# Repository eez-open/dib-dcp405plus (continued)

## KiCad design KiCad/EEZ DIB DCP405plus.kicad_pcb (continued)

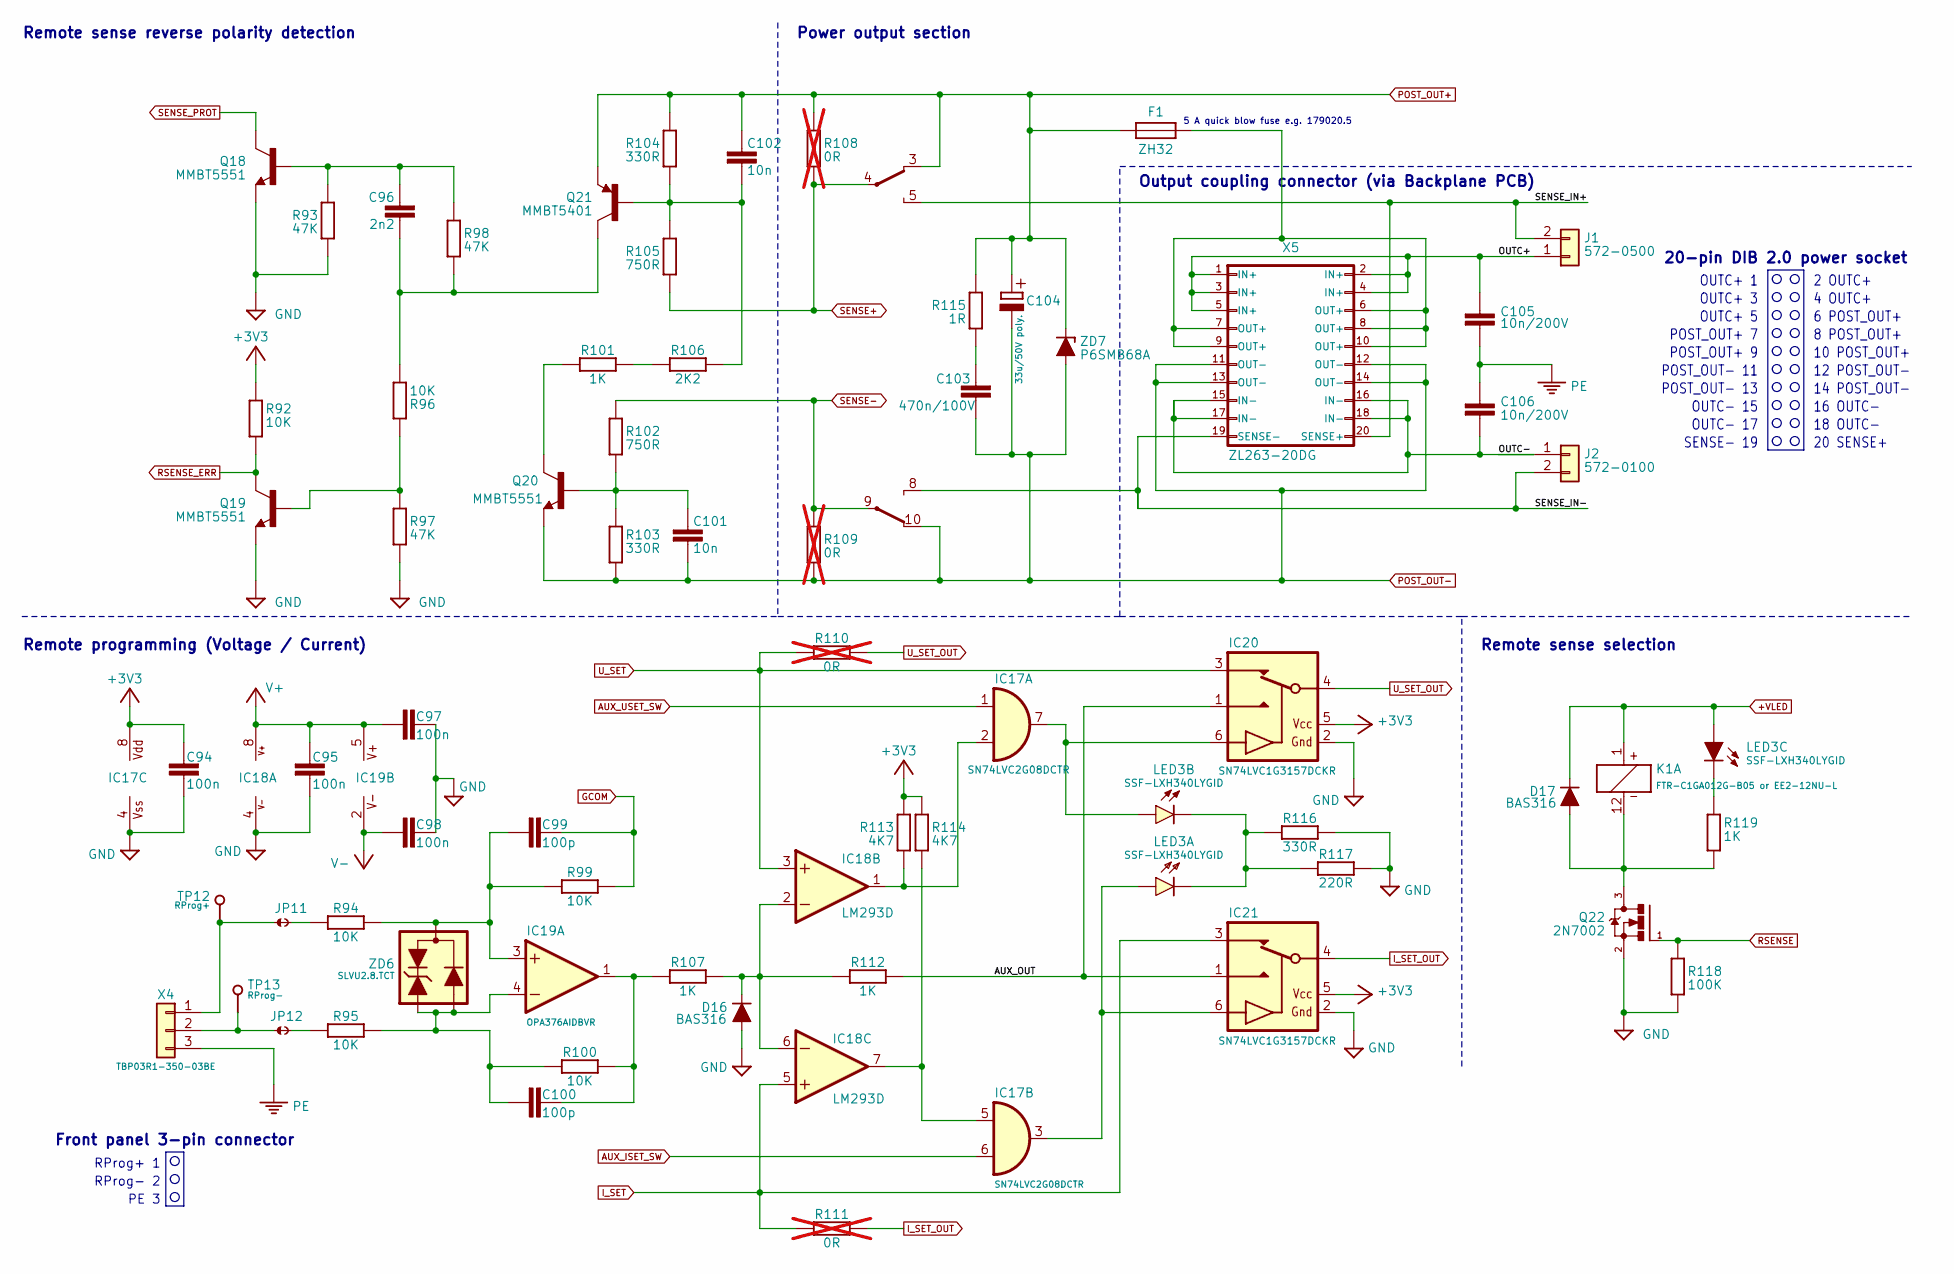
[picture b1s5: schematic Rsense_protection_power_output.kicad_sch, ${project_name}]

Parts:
C94, C95, C97, C98: 100n; C_0603_1608Metric; DigiKey 1276-6717-1-ND
C96: 2n2; C_0805_2012Metric; DigiKey 1276-2478-1-ND
C99, C100: 100p; C_0805_2012Metric; DigiKey 399-15000-1-ND
C101, C102: 10n; C_0805_2012Metric; DigiKey 490-7194-1-ND
C103: 470n/100V; C_0805_2012Metric; DigiKey 587-5014-1-ND
C104: 33u/50V poly.; CAPAE830X1050N; DigiKey 565-HHXD630ARA330MHA0GCT-ND
C105, C106: 10n/200V; C_1206_3216Metric; DigiKey 311-4491-1-ND
D16, D17: BAS316; SOD-323_1P8X1P35_ONS-M; DigiKey 5399-BAS316CT-ND
F1: ZH32; DigiKey 732-11370-ND
IC17: SN74LVC2G08DCTR; DCT8; DigiKey 1727-5987-1-ND
IC18: LM293D; SOIC127P600X173-8N; DigiKey LM293DR2GOSCT-ND
IC19: OPA376AIDBVR; SOT23-5L_STM; DigiKey 296-39130-1-ND
IC20, IC21: SN74LVC1G3157DCKR; SOT65P210X110-6N; DigiKey 296-14909-1-ND
J1: 572-0500; Mouser 164-6221
J2: 572-0100; Mouser 164-6220
JP11, JP12: JP2-NOCUT-0805; JP2 shorted (0603)
K1: FTR-C1GA012G-B05 or EE2-12NU-L; FTR-C1; DigiKey 399-10997-1-ND
LED3: SSF-LXH340LYGID; DigiKey SSF-LXH340LYGID-ND
Q18, Q19, Q20: MMBT5551; SOT23-BEC; DigiKey MMBT5551LT1GOSCT-ND
Q21: MMBT5401; SOT23-BEC; DigiKey MMBT5401-FDICT-ND
Q22: 2N7002; SOT103P240X110-3N; DigiKey T2N7002AKLMCT-ND
R92, R94, R95, R96, R99, R100: 10K; R_0805_2012Metric; DigiKey 311-10.0KCRCT-ND
R93, R97, R98: 47K; R_0805_2012Metric; DigiKey RHM47KKCT-ND
R101, R107, R112, R119: 1K; R_0805_2012Metric; DigiKey 311-1.00KCRCT-ND
R102, R105: 750R; R_0805_2012Metric; DigiKey A126385CT-ND
R103, R104, R116: 330R; R_0805_2012Metric; DigiKey A129743CT-ND
R106: 2K2; R_0805_2012Metric; DigiKey 311-2.20KCRCT-ND
R108, R109, R110, R111: 0R; R_0603_1608Metric; not fitted
R113, R114: 4K7; R_0805_2012Metric; DigiKey 311-4.70KCRCT-ND
R115: 1R; R_0805_2012Metric; DigiKey 13-RC0805FR-131RLCT-ND
R117: 220R; R_0805_2012Metric; DigiKey RMCF0805FT220RCT-ND
R118: 100K; R_0805_2012Metric; DigiKey RMCF0805FT100KCT-ND
TP12, TP13: PCB_TEST_TABSHIELD; Testhole 24_50mils
X4: TBP03R1-350-03BE; DigiKey 2223-TBP03R1-350-03BE-ND
X5: ZL263-20DG; SSW-110-02-T-D-RA; DigiKey PPPC102LJBN-RC
ZD6: SLVU2.8.TCT; SOT23-3; DigiKey SLVU2.8.TCTCT-ND
ZD7: P6SMB68A; DO214AA; DigiKey P6SMB68ABBCT-ND

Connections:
+3V3: C94.2, IC17.8 (VDD), IC20.5 (VDD), IC21.5 (VDD), R92.2, R113.1, R114.1; also elsewhere on the board
+VLED: D17.C, K1.1 (C1), LED3.YA; also elsewhere on the board
/Rsense protection, power output, Rprog/AUX_OUT: IC20.1 (NO), IC21.1 (NO), R112.1
/Rsense protection, power output, Rprog/OUTC+: C105.1, J1.1, X5.1 (IN+), X5.2 (IN+), X5.3 (IN+), X5.4 (IN+), X5.5 (IN+)
/Rsense protection, power output, Rprog/OUTC-: C106.2, J2.1, X5.15 (IN-), X5.16 (IN-), X5.17 (IN-), X5.18 (IN-)
/Rsense protection, power output, Rprog/SENSE_IN+: J1.2, K1.5 (NO), X5.20 (SENSE+)
/Rsense protection, power output, Rprog/SENSE_IN-: J2.2, K1.8 (NO), X5.19 (SENSE-)
AUX_ISET_SW: IC17.6 (I1); also elsewhere on the board
AUX_USET_SW: IC17.1 (I0); also elsewhere on the board
GCOM: C99.1, R99.1; also elsewhere on the board
GND: C94.1, C95.2, C97.2, C98.2, D16.A, IC17.4 (VSS), IC18.4 (V-), IC20.2 (GND), IC21.2 (GND), Q18.E, Q19.E, Q22.2 (S), R93.1, R97.1, R116.1, R117.1, R118.1; also elsewhere on the board
I_SET: IC18.5 (+IN), IC21.3 (NC), R111.2; also elsewhere on the board
I_SET_OUT: IC21.4 (COM), R111.1; also elsewhere on the board
unnamed: C96.1, Q18.B, R93.2, R98.2
unnamed: C96.2, Q21.C, R96.2, R98.1
unnamed: C101.1, Q20.B, R102.1, R103.2
unnamed: C102.2, Q21.B, R104.1, R105.2, R106.2
unnamed: C103.2, R115.2
unnamed: F1.2, X5.6 (OUT+), X5.7 (OUT+), X5.8 (OUT+), X5.9 (OUT+), X5.10 (OUT+)
unnamed: IC17.2 (I1), IC18.1 (OUT), R113.2
unnamed: IC17.7 (O), IC20.6 (CTRL), LED3.GA
unnamed: IC17.5 (I0), IC18.7 (OUT), R114.2
unnamed: IC17.3 (O), IC21.6 (CTRL), LED3.RA
unnamed: D16.C, IC18.2 (-IN), IC18.6 (-IN), R107.1, R112.2
unnamed: C99.2, IC19.3 (+IN), R94.1, R99.2, ZD6.3
unnamed: C100.2, IC19.4 (-IN), R95.1, R100.2, ZD6.1, ZD6.2
unnamed: C100.1, IC19.1 (OUT), R100.1, R107.2
unnamed: JP11.2, R94.2
unnamed: JP12.2, R95.2
unnamed: D17.A, K1.12 (C2), Q22.3 (D), R119.1
unnamed: LED3.GC, LED3.RC, R116.2, R117.2
unnamed: LED3.YC, R119.2
unnamed: Q19.B, R96.1, R97.2
unnamed: Q20.C, R101.1
unnamed: R101.2, R106.1
unnamed: JP11.1, TP12.1 (P$1_1), X4.1
unnamed: JP12.1, TP13.1 (P$1_1), X4.2
PE: C105.2, C106.1, X4.3; also elsewhere on the board
POST_OUT+: C102.1, C104.+, F1.1, K1.3 (NC), Q21.E, R104.2, R108.1, R115.1, ZD7.C; also elsewhere on the board
POST_OUT-: C101.2, C103.1, C104.-, K1.10 (NC), Q20.E, R103.1, R109.2, X5.11 (OUT-), X5.12 (OUT-), X5.13 (OUT-), X5.14 (OUT-), ZD7.A; also elsewhere on the board
RSENSE: Q22.1 (G), R118.2; also elsewhere on the board
RSENSE_ERR: Q19.C, R92.1; also elsewhere on the board
SENSE+: K1.4 (COM), R105.1, R108.2; also elsewhere on the board
SENSE-: K1.9 (COM), R102.2, R109.1; also elsewhere on the board
SENSE_PROT: Q18.C; also elsewhere on the board
U_SET: IC18.3 (+IN), IC20.3 (NC), R110.2; also elsewhere on the board
U_SET_OUT: IC20.4 (COM), R110.1; also elsewhere on the board
V+: C95.1, C97.1, IC18.8 (V+), IC19.5 (V+); also elsewhere on the board
V-: C98.1, IC19.2 (V-); also elsewhere on the board

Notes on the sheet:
8 POST_OUT+
PE 3
16 OUTC-
POST_OUT- 11
12 POST_OUT-
Remote sense reverse polarity detection
POST_OUT+ 9
OUTC- 17
Output coupling connector (via Backplane PCB)
POST_OUT- 13
Remote programming (Voltage / Current)
10 POST_OUT+
4 OUTC+
6 POST_OUT+
2 OUTC+
OUTC+ 5
14 POST_OUT-
18 OUTC-
POST_OUT+ 7
OUTC+ 1
RProg+ 1
20 SENSE+
Front panel 3-pin connector
OUTC+ 3
5 A quick blow fuse e.g. 179020.5
RProg- 2
Power output section
Remote sense selection
SENSE- 19
OUTC- 15
20-pin DIB 2.0 power socket

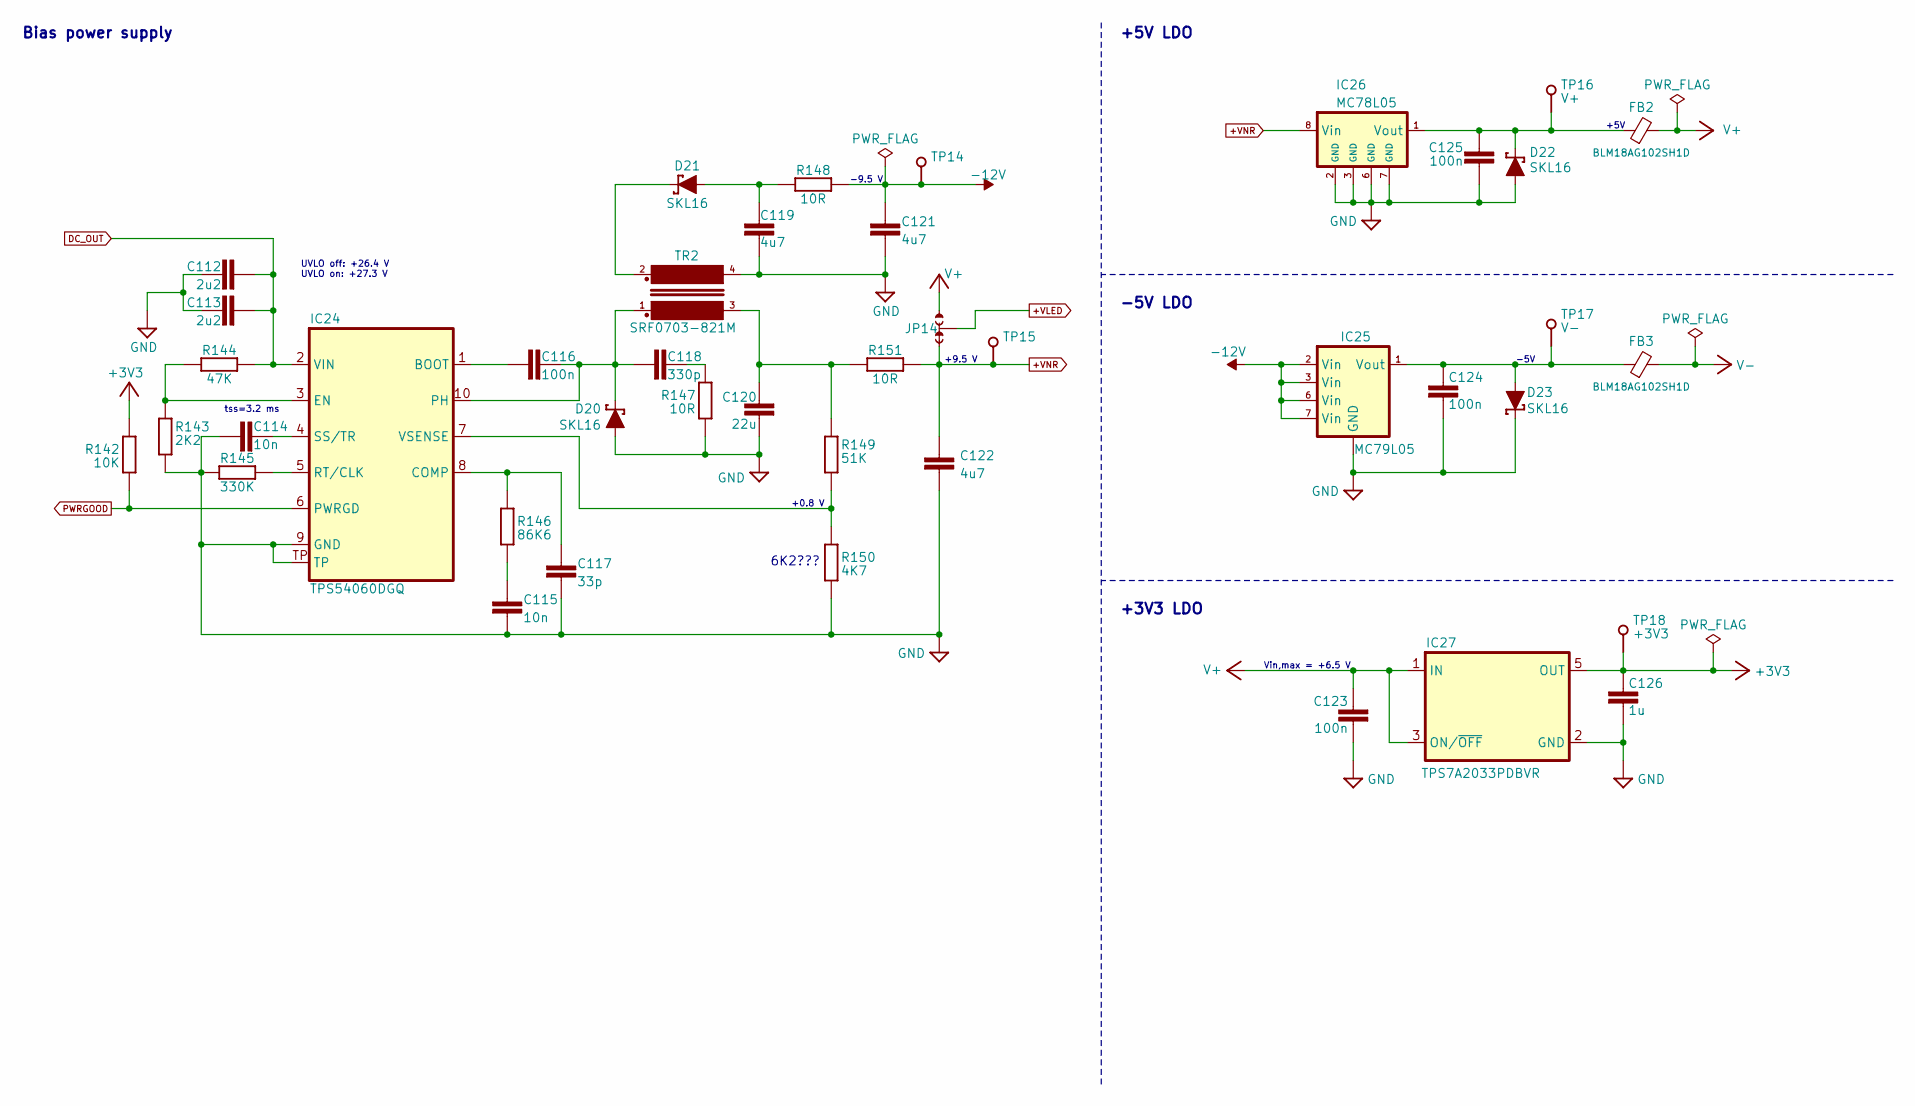
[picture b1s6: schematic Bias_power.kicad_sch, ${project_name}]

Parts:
C112, C113: 2u2; C_1206_3216Metric; DigiKey 1276-3138-1-ND
C114, C115: 10n; C_0805_2012Metric; DigiKey 490-7194-1-ND
C116, C123, C124, C125: 100n; C_0603_1608Metric; DigiKey 1276-6717-1-ND
C117: 33p; C_0805_2012Metric; DigiKey 399-C0805C330J5GACTUCT-ND
C118: 330p; C_0805_2012Metric; DigiKey 311-1117-1-ND
C119, C121, C122: 4u7; C_0805_2012Metric; DigiKey 1276-2415-1-ND
C120: 22u; C_1210_3225Metric; DigiKey 1276-1851-1-ND
C126: 1u; C_0805_2012Metric; DigiKey 1276-2931-1-ND
D20, D21, D22, D23: SKL16; SOD123; DigiKey RB160MM-60CT-ND
FB2, FB3: BLM18AG102SH1D; BEAD0603; DigiKey 490-7809-1-ND
IC24: TPS54060DGQ; SOP50P490X110-11N; DigiKey 296-37148-1-ND
IC25: MC79L05; SOIC127P600X173-8N; DigiKey MC79L05ACDR2GOSCT-ND
IC26: MC78L05; SOIC127P600X173-8N; DigiKey MC78L05ACDR2GOSCT-ND
IC27: TPS7A2033PDBVR; SOT23-5L_STM; DigiKey 296-TPS7A2033PDBVRCT-ND
JP14: JP3 shorted (0603)
R142: 10K; R_0805_2012Metric; DigiKey 311-10.0KCRCT-ND
R143: 2K2; R_0805_2012Metric; DigiKey 311-2.20KCRCT-ND
R144: 47K; R_0805_2012Metric; DigiKey RHM47KKCT-ND
R145: 330K; R_0805_2012Metric; DigiKey A126361CT-ND
R146: 86K6; R_0805_2012Metric; DigiKey 311-86.6KCRCT-ND
R147, R148, R151: 10R; R_0805_2012Metric; DigiKey 311-10.0CRCT-ND
R149: 51K; R_0805_2012Metric; DigiKey 311-51.0KCRCT-ND
R150: 4K7; R_0805_2012Metric; DigiKey 311-4.70KCRCT-ND
TP14, TP15, TP16, TP17, TP18: TEST-PIN_0.9MM; Testhole 24_50mils
TR2: SRF0703-821M; SRF0703; DigiKey SRF0703-821MCT-ND

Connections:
+3V3: C126.2, IC27.5 (OUT), R142.1, TP18.1 (P$1_1); also elsewhere on the board
+VLED: JP14.COM; also elsewhere on the board
+VNR: C122.1, IC26.8 (Vin), JP14.NC, R151.2, TP15.1 (P$1_1); also elsewhere on the board
-12V: C121.1, IC25.2 (Vin), IC25.3 (Vin), IC25.6 (Vin), IC25.7 (Vin), R148.2, TP14.1 (P$1_1); also elsewhere on the board
DC_OUT: C112.1, C113.1, IC24.2 (VIN), R144.2; also elsewhere on the board
GND: C112.2, C113.2, C114.2, C115.1, C117.1, C119.2, C120.2, C121.2, C122.2, C123.1, C124.1, C125.2, C126.1, D20.A, D22.A, D23.C, IC24.9 (GND), IC24.TP, IC25.5 (GND), IC26.2 (GND), IC26.3 (GND), IC26.6 (GND), IC26.7 (GND), IC27.2 (GND), R143.1, R145.1, R147.2, R150.2, TR2.4; also elsewhere on the board
unnamed: C115.2, R146.1
unnamed: C118.2, R147.1
unnamed: C119.1, D21.A, R148.1
unnamed: C120.1, R149.1, R151.1, TR2.3
unnamed: D21.C, TR2.2
unnamed: C116.2, IC24.1 (BOOT)
unnamed: C117.2, IC24.8 (COMP), R146.2
unnamed: IC24.3 (EN), R143.2, R144.1
unnamed: C116.1, C118.1, D20.C, IC24.10 (PH), TR2.1
unnamed: IC24.5 (RT/CLK), R145.2
unnamed: C114.1, IC24.4 (SS/TR)
unnamed: IC24.7 (VSENSE), R149.2, R150.1
unnamed: C124.2, D23.A, FB3.1, IC25.1 (Vout), TP17.1 (P$1_1)
unnamed: C125.1, D22.C, FB2.1, IC26.1 (Vout), TP16.1 (P$1_1)
PWRGOOD: IC24.6 (PWRGD), R142.2; also elsewhere on the board
V+: C123.2, FB2.2, IC27.1 (IN), IC27.3 (ON/~OFF), JP14.NO; also elsewhere on the board
V-: FB3.2; also elsewhere on the board

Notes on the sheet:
+5V
UVLO off: +26.4 V UVLO on: +27.3 V
Vin,max = +6.5 V
+5V LDO
Bias power supply
-5V LDO
+0.8 V
+3V3 LDO
6K2???
-5V
-9.5 V
tss=3.2 ms
+9.5 V

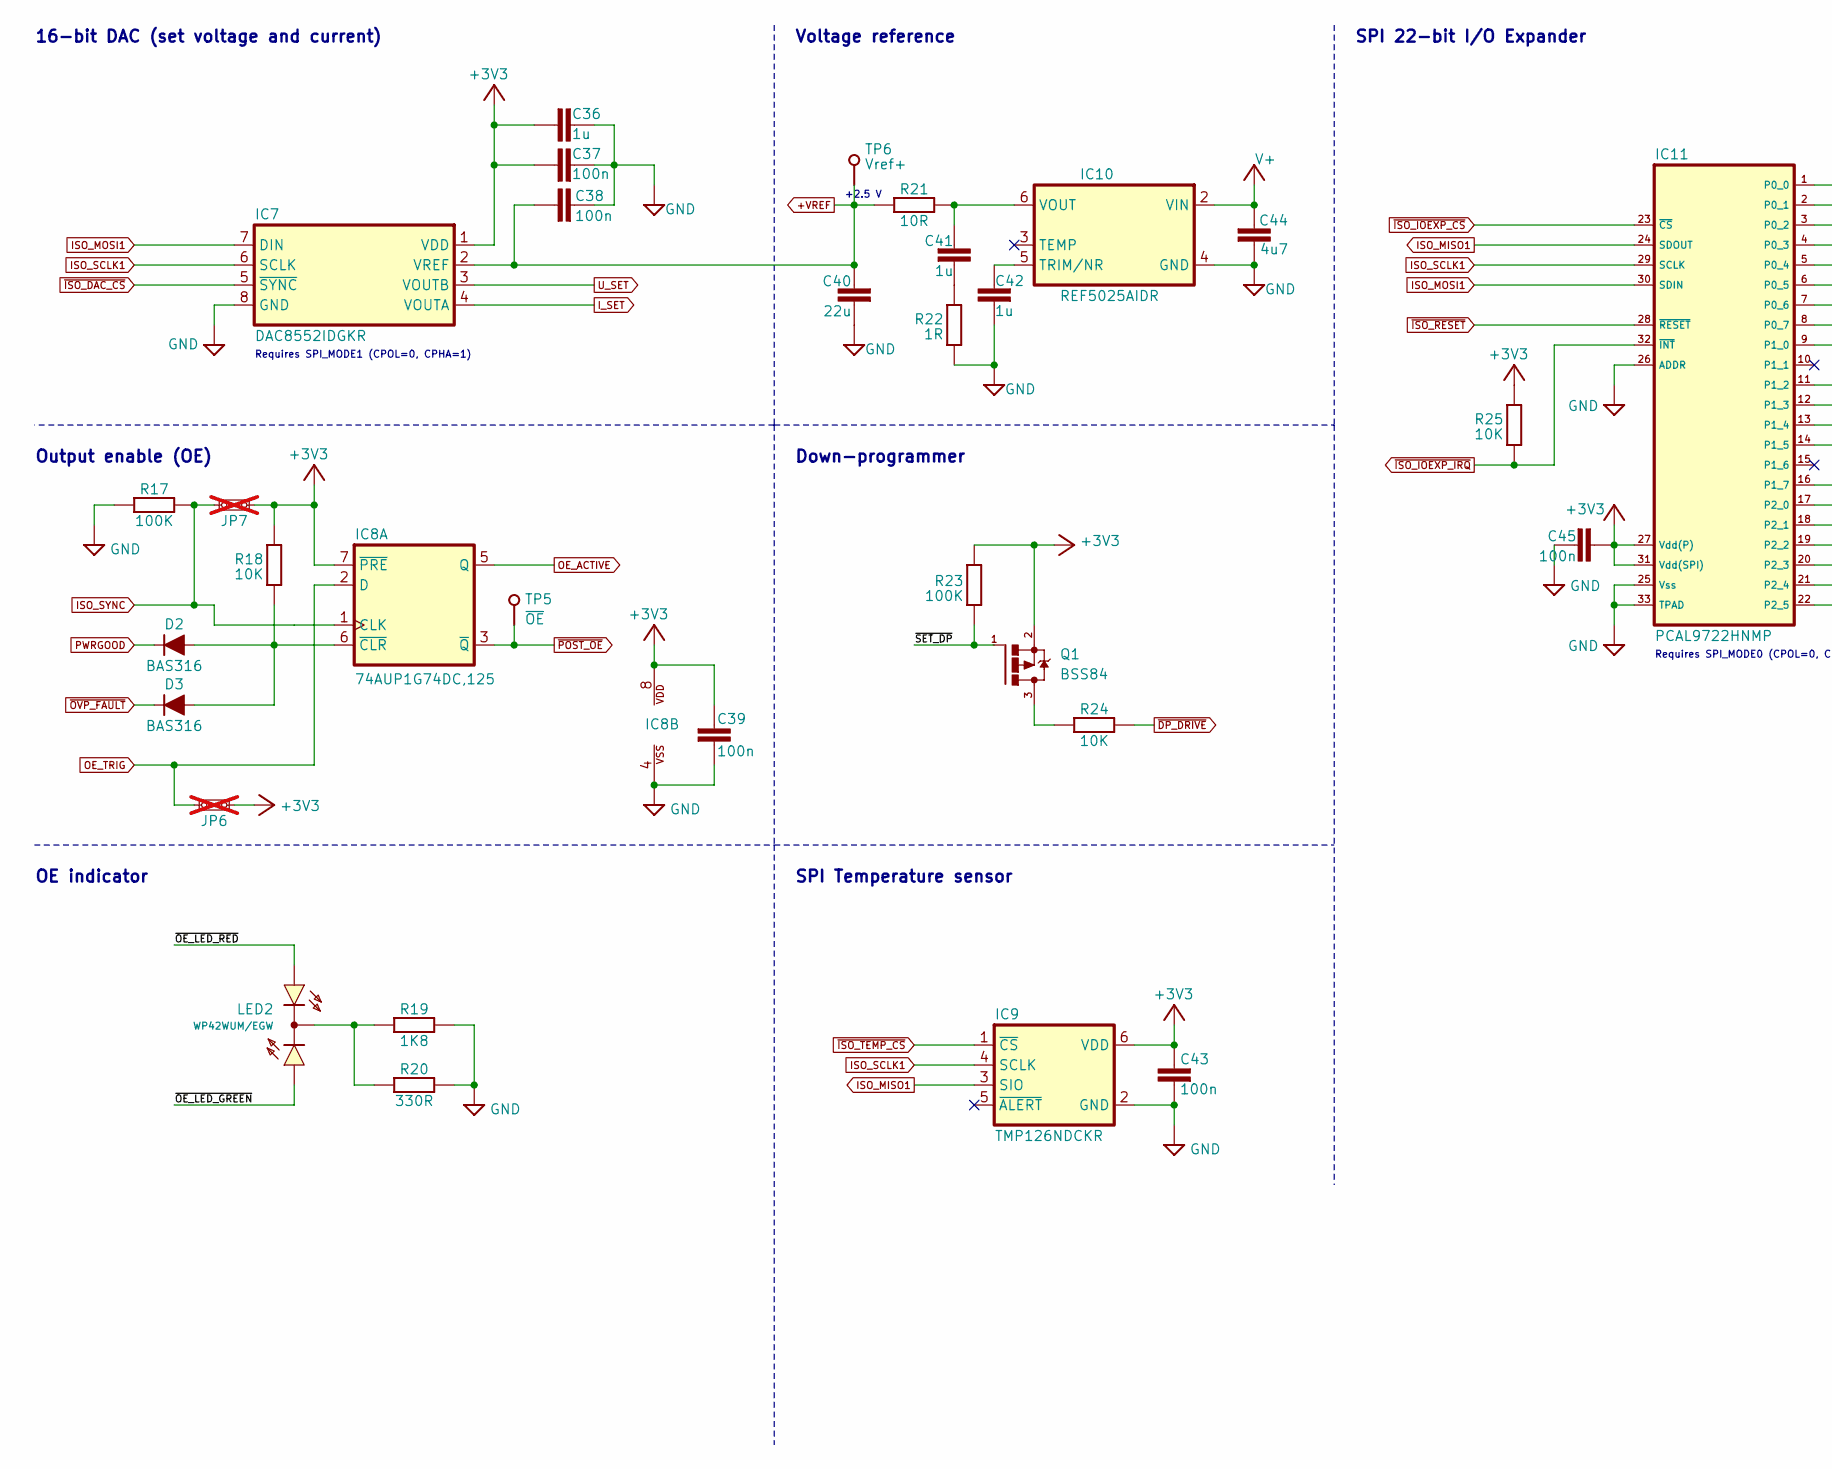
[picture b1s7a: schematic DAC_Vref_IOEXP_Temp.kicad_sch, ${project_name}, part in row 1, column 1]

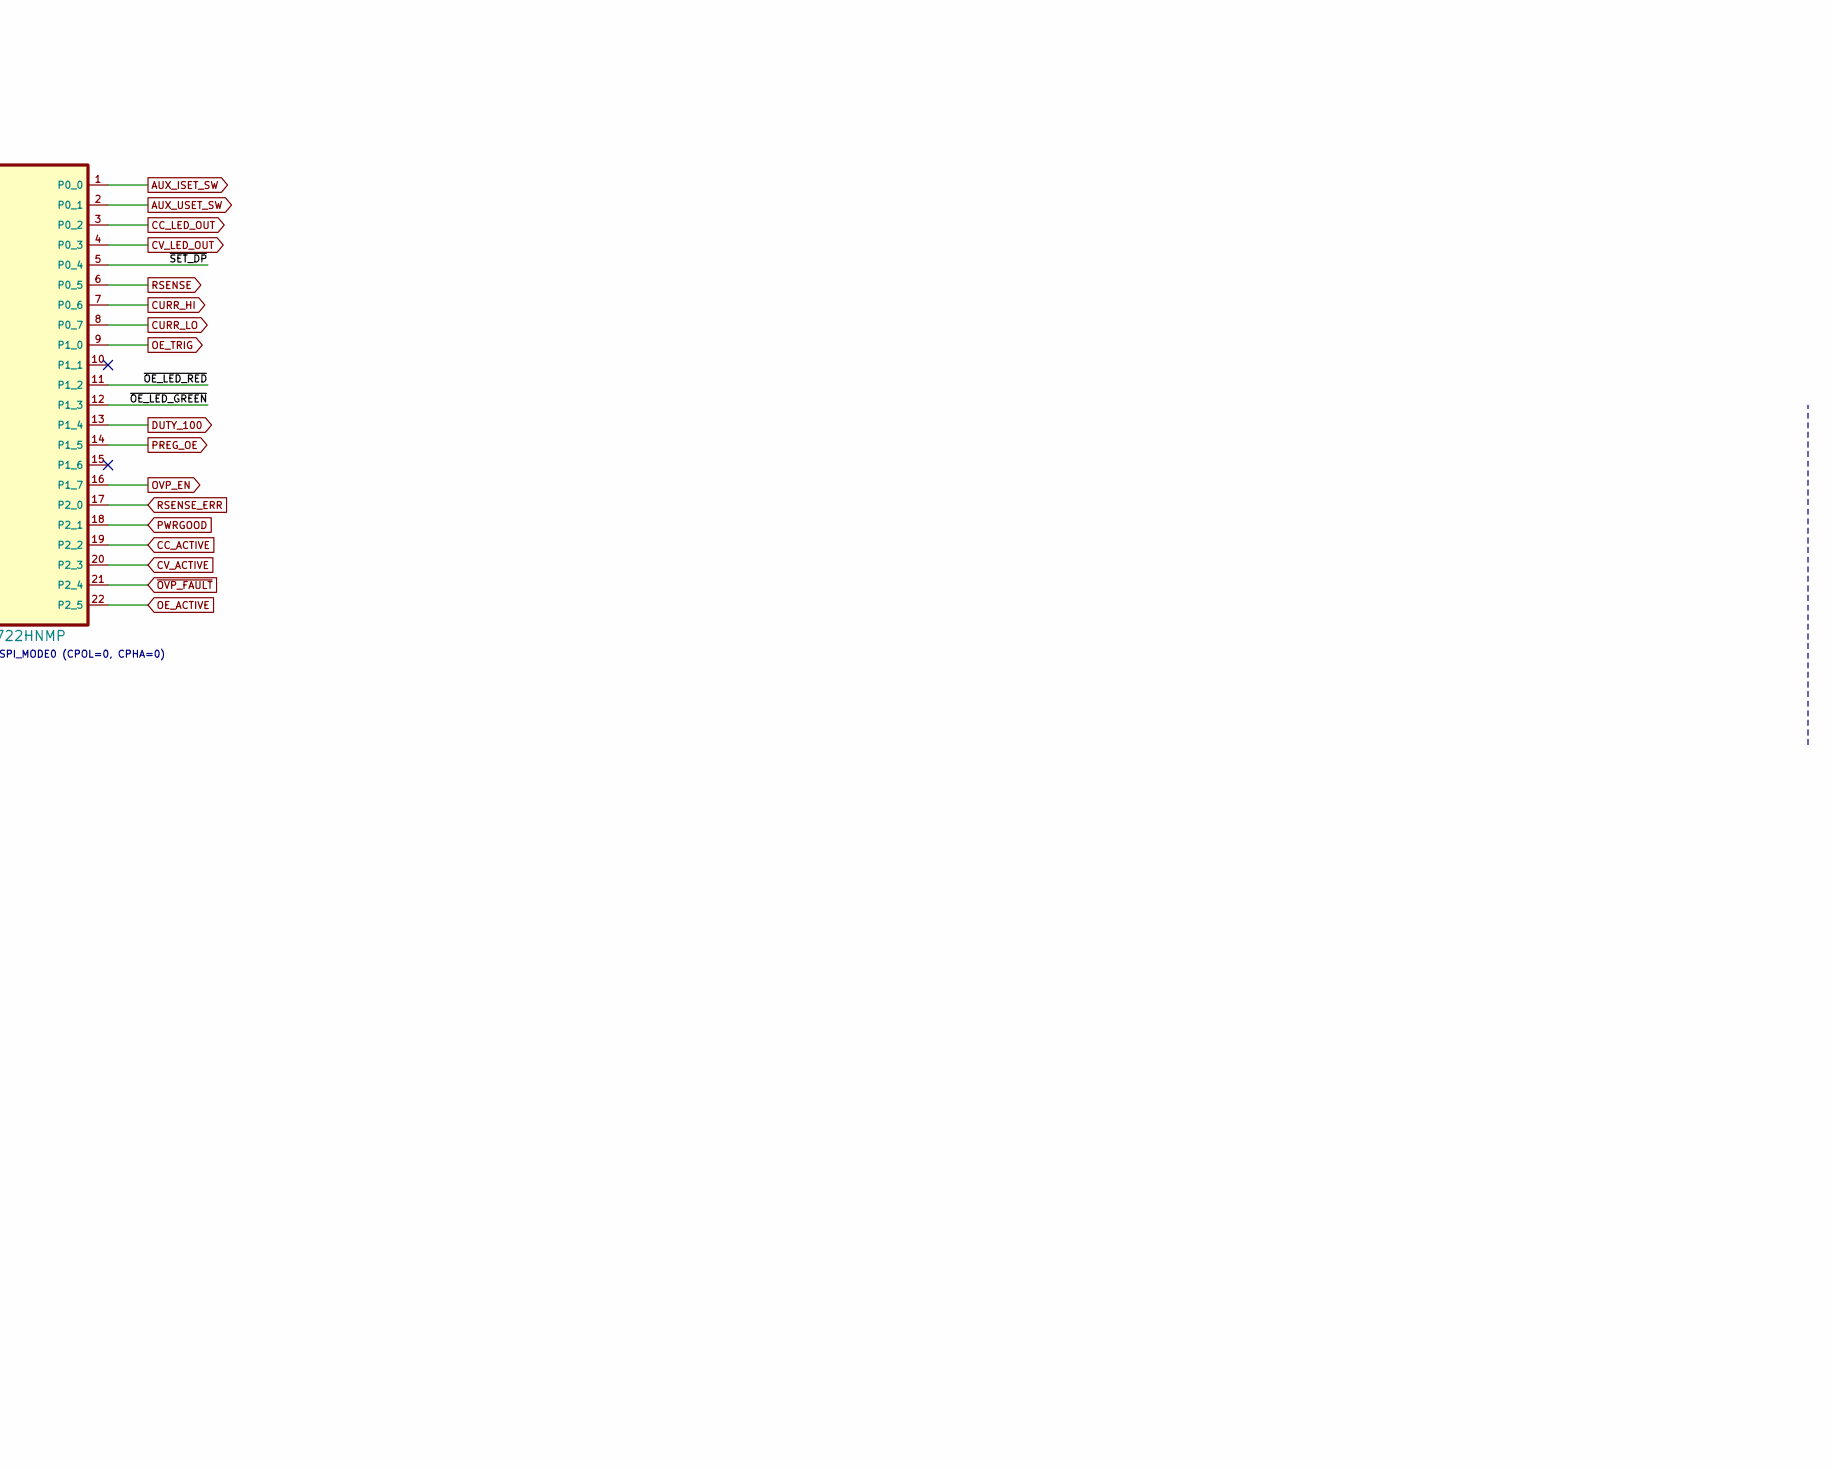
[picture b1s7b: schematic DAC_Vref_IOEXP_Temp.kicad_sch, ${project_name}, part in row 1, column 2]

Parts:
C36, C41, C42: 1u; C_0805_2012Metric; DigiKey 1276-2931-1-ND
C37, C38, C39, C43, C45: 100n; C_0603_1608Metric; DigiKey 1276-6717-1-ND
C40: 22u; C_1210_3225Metric; DigiKey 1276-1851-1-ND
C44: 4u7; C_0805_2012Metric; DigiKey 1276-2415-1-ND
D2, D3: BAS316; SOD-323_1P8X1P35_ONS-M; DigiKey 5399-BAS316CT-ND
IC7: DAC8552IDGKR; DGK8-M; DigiKey 296-46082-1-ND
IC8: 74AUP1G74DC,125; DCU8; DigiKey 1727-74AUP1G74DC-Q100HCT-ND
IC9: TMP126NDCKR; DCK6; DigiKey 296-TMP126NDCKRCT-ND
IC10: REF5025AIDR; SOIC127P600X173-8N; DigiKey 296-41382-1-ND
IC11: PCAL9722HNMP; HVQFN32_SOT617-1_NXP-M; DigiKey 568-PCAL9722HNMPCT-ND
JP6, JP7: M22-2010246; DigiKey M22-2010346-ND; not fitted
LED2: WP42WUM/EGW; L-42WUM-1EGWT; DigiKey 754-1718-ND
Q1: BSS84; SOT103P240X110-3N; DigiKey BSS84LT1GOSCT-ND
R17, R23: 100K; R_0805_2012Metric; DigiKey RMCF0805FT100KCT-ND
R18, R24, R25: 10K; R_0805_2012Metric; DigiKey 311-10.0KCRCT-ND
R19: 1K8; R_0805_2012Metric; DigiKey 311-1.80KCRCT-ND
R20: 330R; R_0805_2012Metric; DigiKey A129743CT-ND
R21: 10R; R_0805_2012Metric; DigiKey 311-10.0CRCT-ND
R22: 1R; R_0805_2012Metric; DigiKey 13-RC0805FR-131RLCT-ND
TP5: TEST-PIN_0.9MM; Testhole 24_50mils
TP6: PCB_TEST_TABSHIELD; Testhole 24_50mils

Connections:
+3V3: C36.1, C37.2, C39.2, C43.1, C45.2, IC7.1 (VDD), IC8.7 (~PRE), IC8.8 (VDD), IC9.6 (VDD), IC11.27 (Vdd(P)), IC11.31 (Vdd(SPI)), JP6.1, JP7.1, Q1.2 (S), R18.2, R23.1, R25.2; also elsewhere on the board
+VREF: C38.2, C40.1, IC7.2 (VREF), R21.1, TP6.1 (P$1_1); also elsewhere on the board
/DAC, OE, Vref, IOEXP, Temp/~OE_LED_GREEN: IC11.12 (P1_3), LED2.GREEN (AG)
/DAC, OE, Vref, IOEXP, Temp/~OE_LED_RED: IC11.11 (P1_2), LED2.RED (AR)
/DAC, OE, Vref, IOEXP, Temp/~SET_DP: IC11.5 (P0_4), Q1.1 (G), R23.2
AUX_ISET_SW: IC11.1 (P0_0); also elsewhere on the board
AUX_USET_SW: IC11.2 (P0_1); also elsewhere on the board
CC_ACTIVE: IC11.19 (P2_2); also elsewhere on the board
CC_LED_OUT: IC11.3 (P0_2); also elsewhere on the board
CURR_HI: IC11.7 (P0_6); also elsewhere on the board
CURR_LO: IC11.8 (P0_7); also elsewhere on the board
CV_ACTIVE: IC11.20 (P2_3); also elsewhere on the board
CV_LED_OUT: IC11.4 (P0_3); also elsewhere on the board
DUTY_100: IC11.13 (P1_4); also elsewhere on the board
GND: C36.2, C37.1, C38.1, C39.1, C40.2, C42.2, C43.2, C44.2, C45.1, IC7.8 (GND), IC8.4 (VSS), IC9.2 (GND), IC10.4 (GND), IC11.25 (Vss), IC11.26 (ADDR), IC11.33 (TPAD), R17.1, R19.2, R20.2, R22.2; also elsewhere on the board
ISO_MISO1: IC9.3 (SIO), IC11.24 (SDOUT); also elsewhere on the board
ISO_MOSI1: IC7.7 (DIN), IC11.30 (SDIN); also elsewhere on the board
ISO_SCLK1: IC7.6 (SCLK), IC9.4 (SCLK), IC11.29 (SCLK); also elsewhere on the board
ISO_SYNC: IC8.1 (CLK), JP7.2, R17.2; also elsewhere on the board
I_SET: IC7.4 (VOUTA); also elsewhere on the board
unnamed: C41.2, R22.1
unnamed: D2.A, D3.A, IC8.6 (~CLR), R18.1
unnamed: C42.1, IC10.5 (TRIM/NR)
unnamed: C41.1, IC10.6 (VOUT), R21.2
unnamed: LED2.CC (C), R19.1, R20.1
unnamed: Q1.3 (D), R24.2
OE_ACTIVE: IC8.5 (Q), IC11.22 (P2_5)
OE_TRIG: IC8.2 (D), IC11.9 (P1_0), JP6.2
OVP_EN: IC11.16 (P1_7); also elsewhere on the board
PREG_OE: IC11.14 (P1_5); also elsewhere on the board
PWRGOOD: D2.C, IC11.18 (P2_1); also elsewhere on the board
RSENSE: IC11.6 (P0_5); also elsewhere on the board
RSENSE_ERR: IC11.17 (P2_0); also elsewhere on the board
U_SET: IC7.3 (VOUTB); also elsewhere on the board
V+: C44.1, IC10.2 (VIN); also elsewhere on the board
~DP_DRIVE: R24.1; also elsewhere on the board
~ISO_DAC_CS: IC7.5 (~SYNC); also elsewhere on the board
~ISO_IOEXP_CS: IC11.23 (~CS); also elsewhere on the board
~ISO_IOEXP_IRQ: IC11.32 (~INT), R25.1; also elsewhere on the board
~ISO_RESET: IC11.28 (~RESET); also elsewhere on the board
~ISO_TEMP_CS: IC9.1 (~CS); also elsewhere on the board
~OVP_FAULT: D3.C, IC11.21 (P2_4); also elsewhere on the board
~POST_OE: IC8.3 (~Q), TP5.1 (P$1_1); also elsewhere on the board

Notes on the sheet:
Voltage reference
Requires SPI_MODE0 (CPOL=0, CPHA=0)
Down-programmer
Requires SPI_MODE1 (CPOL=0, CPHA=1)
Output enable (OE)
16-bit DAC (set voltage and current)
+2.5 V
SPI Temperature sensor
OE indicator
SPI 22-bit I/O Expander
